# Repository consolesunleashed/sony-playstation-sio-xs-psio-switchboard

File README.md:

# Sony PlayStation SIO-XS PSIO Quick Solder Switchboard

SIO-X is an elegant PSIO switchboard designed by Voultar to make switchboard installs simpler and neater. It comes with the addition of an on-board modchip, quick solder board design, and a number of other improvements over the standard PSIO switchboard.

## What is SIO-XS?

For my own uses I prefer a separate modchip install so I decided to design the SIO-XS. The SIO-SX simplifies Voultar’s PSIO switchboard design by omitting the modchip and changing the layout a little. My design is focused on making installs as aesthetically pleasing as possible so an additional wire pad was added to prevent any crossed wire runs as well as 45 degree pad placement so wires can be run to the back of the pads or to the front of them. Check the install photos folder to see how these design ideas work in practice.

## Why is it called SIO-XS?

SIO-XS for eXtra Small. SIO-XS for Sans, in that it is sans-modchip. SIO-XS in that it removes the ‘excess’ so it is just a PSIO switchboard.

## Version History

- SIO-XS v1.0 - 30/09/2021
- SIO-XS v1.1 - 10/06/2023

## Credits and Attributions

SIO-XS was designed from the ground up but is based entirely on Voultar’s work and SIO-X. So all credit to Voultar.

## License

If you use this in any way, shape or form, you must include a link back to this repository and mention me by name on any sales pages and social media posts. Not only will this help me to keep designing mod kits and offering them to the community, but it is basic common courtesy as well. Don't be a douchebag. :)

## Donate

Working on designs to release for free can be both time consuming and expensive. If you like what I do, a small donation will go a long way in helping me continue to serve the modding community as best as I can, with many more free and original guides, designs, and ideas to come.

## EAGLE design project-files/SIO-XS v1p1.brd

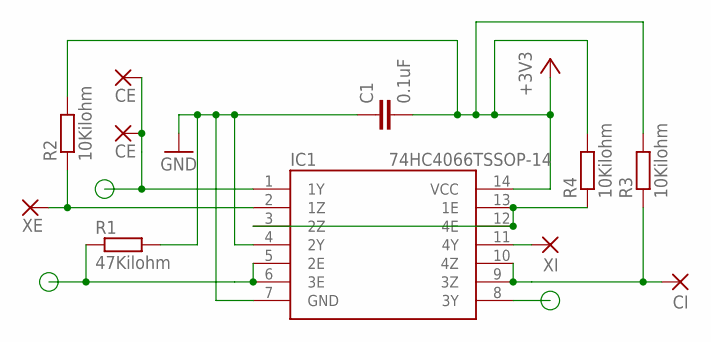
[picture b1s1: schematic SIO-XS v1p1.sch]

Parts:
C1: 0.1uF; C0805
CE, CE1: CE; CIRCLE-1,5X1,5
CI: CI; CIRCLE-1,5X1,5
IC1: 74HC4066TSSOP-14; TSSOP-14
R1: 47Kilohm; R0805
R2, R3, R4: 10Kilohm; R0805
XE: XE; CIRCLE-1,5X1,5
XI: XI; CIRCLE-1,5X1,5

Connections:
+3.3V: C1.2, IC1.14 (VCC), R2.2, R3.2, R4.2
CE: CE.1, CE1.1, IC1.1 (1Y)
CI: CI.1, IC1.9 (3Z), IC1.10 (4Z), R3.1
EN: IC1.5 (2E), IC1.6 (3E), R1.1
GND: C1.1, IC1.4 (2Y), IC1.7 (GND), R1.2
unnamed: IC1.3 (2Z), IC1.12 (4E), IC1.13 (1E), R4.1
XE: IC1.2 (1Z), R2.1, XE.1
XI: IC1.11 (4Y), XI.1

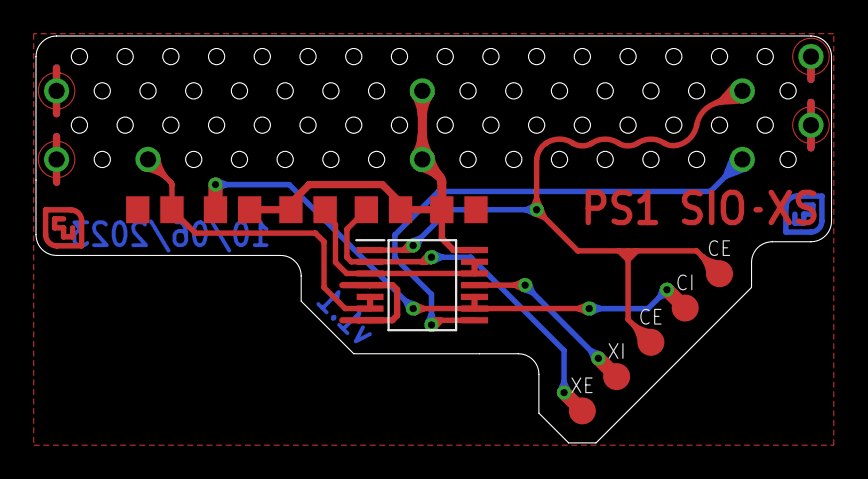
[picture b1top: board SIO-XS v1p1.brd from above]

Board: 2 copper layers, 44.2 x 22.6 mm, 11 parts (0 on the bottom side), 8 nets.

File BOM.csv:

Part,MPN,Value,Case/Size,Amount
Quad SPST Analog Switch,74HC4066,,TSSOP-14,1
Capacitor,,0.1uF / 25V,0803,1
Resistor,,10Kilohm,0803,3
Resistor,,47Kilohm,0803,1
